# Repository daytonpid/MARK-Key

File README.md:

# MARK-Key
A authentication key for MARK ( Mutual Authentication to Resist Keylogging )

## White Paper: http://dx.doi.org/10.1145/2663348

## Implementation: https://www1.cs.fau.de/filepool/projects/mark/index.html

## Purpose: To provide users of the MARK implementation with openly available board design files for the authentication key.

### TODO:

- [x] Update the outdated implementation for use with the latest Linux Kernel

- [ ] Provide Documentation

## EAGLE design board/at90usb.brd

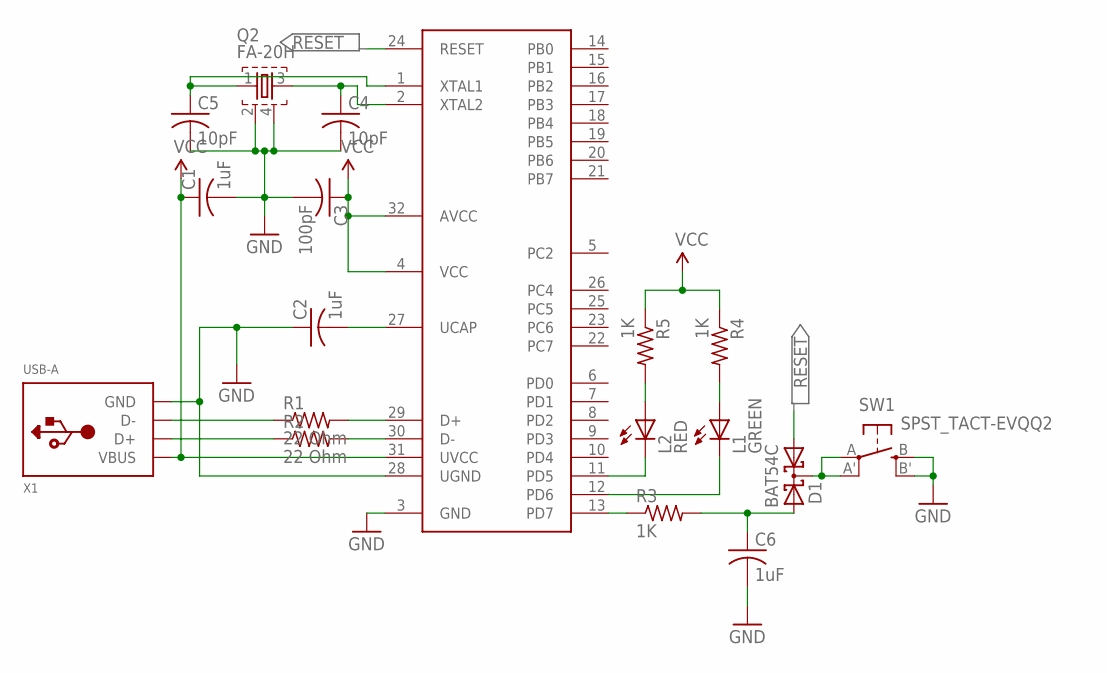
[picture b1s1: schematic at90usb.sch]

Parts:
C1, C2, C6: 1uF; C0805K; MPN 06033D105MAT2A
C3: 100pF; C0805K; MPN 0603YC104K4Z2A
C4, C5: 10pF; C0805
D1: BAT54C; SOT23
L1: GREEN; CHIPLED_1206
L2: RED; CHIPLED_1206
Q2: FA-20H
R1, R2: 22 Ohm; M0805
R3, R4, R5: 1K; M0805
SW1: SPST_TACT-EVQQ2; EVQ-Q2
U1: AT90USB162; VQFP32
X1: USB-A; MOLEX_480371000

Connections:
GND: C1.2, C2.1, C3.2, C4.2, C5.2, C6.2, Q2.2, Q2.4, SW1.B (S), SW1.B' (S1), U1.3 (GND), U1.28 (UGND), X1.4 (GND)
unnamed: R1.2, U1.29 (D+)
unnamed: R2.2, U1.30 (D-)
unnamed: R1.1, X1.2 (D-)
unnamed: R2.1, X1.3 (D+)
unnamed: D1.3 (CC), SW1.A, SW1.A' (P1)
unnamed: C5.1, Q2.1, U1.1 (XTAL1)
unnamed: C2.2, U1.27 (UCAP)
unnamed: C4.1, Q2.3, U1.2 (XTAL2)
unnamed: C6.1, D1.2 (A2), R3.2
unnamed: R3.1, U1.13 (PD7)
unnamed: L1.C, U1.12 (PD6)
unnamed: L1.A, R4.2
unnamed: L2.C, U1.11 (PD5)
unnamed: L2.A, R5.2
RESET: D1.1 (A1), U1.24 (RESET)
VCC: C1.1, C3.1, R4.1, R5.1, U1.4 (VCC), U1.31 (UVCC), U1.32 (AVCC), X1.1 (VBUS)

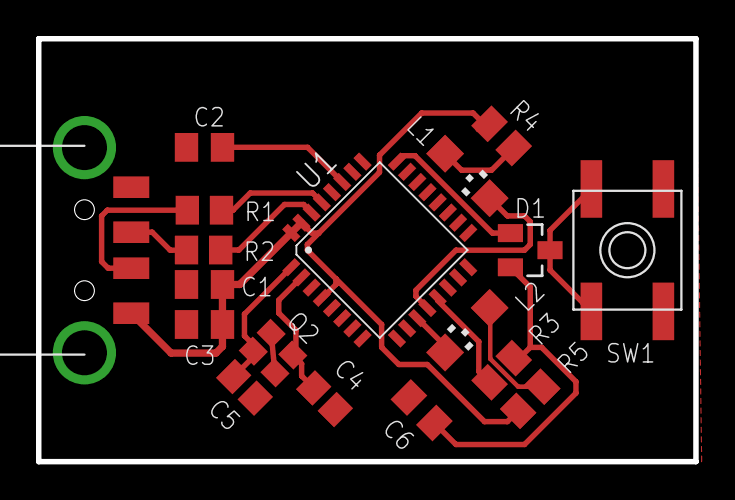
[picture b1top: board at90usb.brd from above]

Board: 2 copper layers, 36.5 x 23.5 mm, 18 parts (0 on the bottom side), 17 nets.

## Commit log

2016-04-06 Init Mark Key
2016-04-06 Added Experimental Teensy3 Support
2016-05-20 TRESOR Kernel Patch (4.6)
    After alot of hard work, here is the most updated kernel patch for tresor
2016-05-20 Legacy TRESOR Kernel Patch
2016-05-21 TRESOR 32bit Patches
    Kernel: 4.6.0, 3.18.5
2016-05-21 Rename tresor-patch-4.6_i686 to tresor-patch-4.6.0_i686
2016-05-21 Rename tresor-patch-4.6_aesni to tresor-patch-4.6.0_aesni
2016-05-27 tresor patches update
2016-09-01 removing patches
